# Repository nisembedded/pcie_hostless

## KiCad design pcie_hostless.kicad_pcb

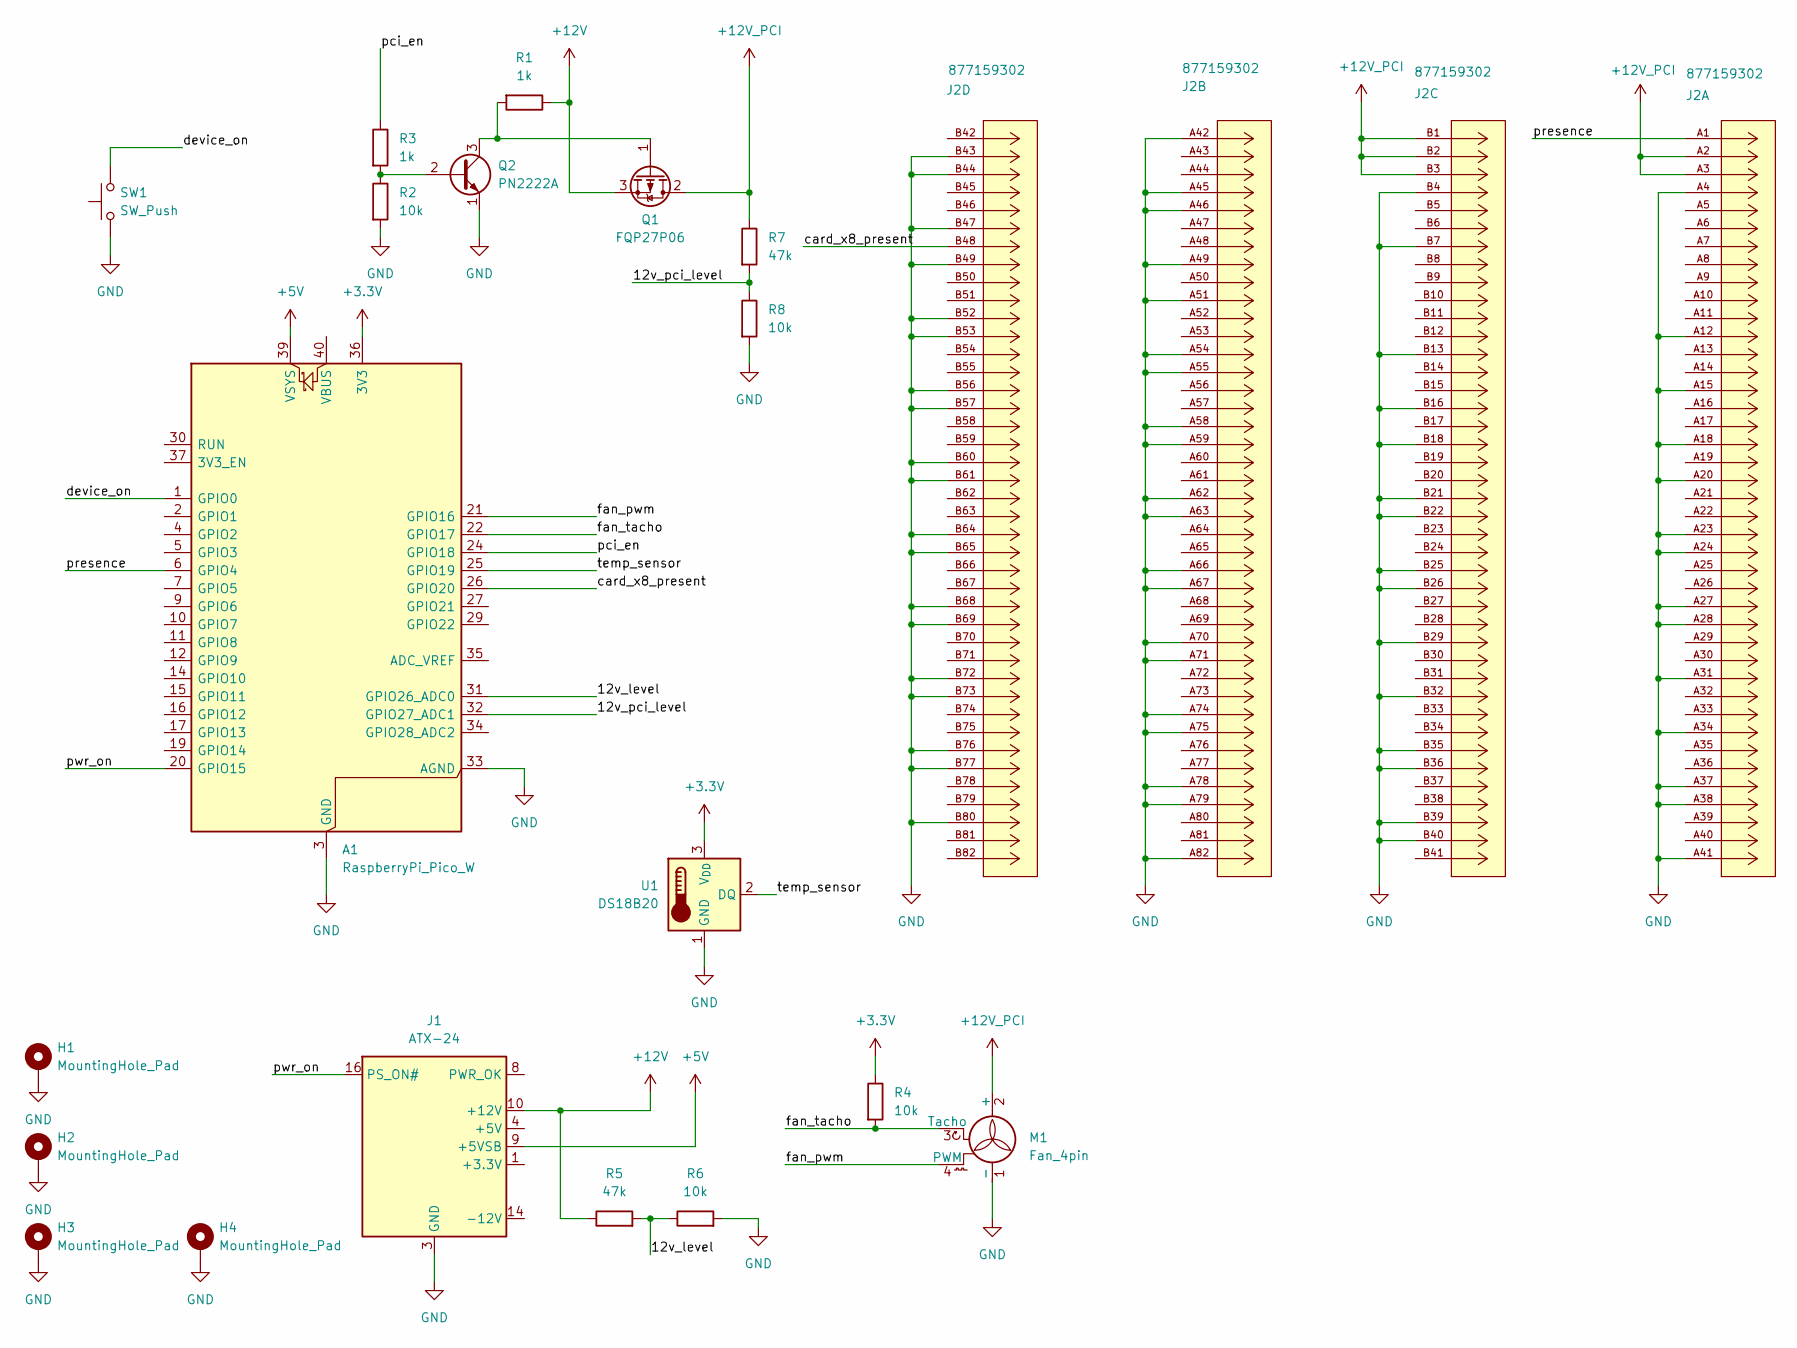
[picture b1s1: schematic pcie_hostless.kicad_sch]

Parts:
A1: RaspberryPi_Pico_W; RaspberryPi_Pico_Common_THT
H1, H2, H3, H4: MountingHole_Pad; MountingHole_3.5mm_Pad_Via
J1: ATX-24; Molex_Mini-Fit_Jr_5566-24A2_2x12_P4.20mm_Vertical
J2: 877159302; CONN_87715-9302_MOL; MANUFACTURER_PART_NUMBER 877159302
M1: Fan_4pin; FanPinHeader_1x04_P2.54mm_Vertical
Q1: FQP27P06; TO-220-3_Vertical
Q2: PN2222A; TO-92_Inline
R1, R3: 1k; R_0805_2012Metric
R2, R4, R6, R8: 10k; R_0805_2012Metric
R5, R7: 47k; R_0805_2012Metric
SW1: SW_Push; SW_Tactile_SKHH_Angled
U1: DS18B20; TO-92_Inline

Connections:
+3.3V: A1.36 (3V3), R4.1, U1.3 (V_{DD})
+5V: A1.39 (VSYS), J1.9 (+5VSB)
+12V: J1.10 (+12V), J1.11 (+12V), Q1.3 (S), R1.1, R5.1
+12V_PCI: J2.A2, J2.A3, J2.B1, J2.B2, J2.B3, M1.2 (+), Q1.2 (D), R7.1
/12v_level: A1.31 (GPIO26_ADC0), R5.2, R6.1
/12v_pci_level: A1.32 (GPIO27_ADC1), R7.2, R8.1
/card_x8_present: A1.26 (GPIO20), J2.B48
/device_on: A1.1 (GPIO0), SW1.2
/fan_pwm: A1.21 (GPIO16), M1.4 (PWM)
/fan_tacho: A1.22 (GPIO17), M1.3 (Tacho), R4.2
/pci_en: A1.24 (GPIO18), R3.1
/presence: A1.6 (GPIO4), J2.A1
/pwr_on: A1.20 (GPIO15), J1.16 (PS_ON#)
/temp_sensor: A1.25 (GPIO19), U1.2 (DQ)
GND: A1.3 (GND), A1.8 (GND), A1.13 (GND), A1.18 (GND), A1.23 (GND), A1.28 (GND), A1.33 (AGND), A1.38 (GND), H1.1, H2.1, H3.1, H4.1, J1.3 (GND), J1.5 (GND), J1.7 (GND), J1.15 (GND), J1.17 (GND), J1.18 (GND), J1.19 (GND), J1.24 (GND), J2.A4, J2.A12, J2.A15, J2.A18, J2.A20, J2.A23, J2.A24, J2.A27, J2.A28, J2.A31, J2.A34, J2.A37, J2.A38, J2.A41, J2.A42, J2.A45, J2.A46, J2.A49, J2.A51, J2.A54, J2.A55, J2.A58, J2.A59, J2.A62, J2.A63, J2.A66, J2.A67, J2.A70, J2.A71, J2.A74, J2.A75, J2.A78, J2.A79, J2.A82, J2.B4, J2.B7, J2.B13, J2.B16, J2.B18, J2.B21, J2.B22, J2.B25, J2.B26, J2.B29, J2.B32, J2.B35, J2.B36, J2.B39, J2.B40, J2.B43, J2.B44, J2.B47, J2.B49, J2.B52, J2.B53, J2.B56, J2.B57, J2.B60, J2.B61, J2.B64, J2.B65, J2.B68, J2.B69, J2.B72, J2.B73, J2.B76, J2.B77, J2.B80, M1.1 (-), Q2.1 (E), R2.2, R6.2, R8.2, SW1.1, U1.1 (GND)
unnamed: J1.1 (+3.3V), J1.2 (+3.3V), J1.12 (+3.3V), J1.13 (+3.3V)
unnamed: J1.4 (+5V), J1.6 (+5V), J1.21 (+5V), J1.22 (+5V), J1.23 (+5V)
unnamed: Q1.1 (G), Q2.3 (C), R1.2
unnamed: Q2.2 (B), R2.1, R3.2

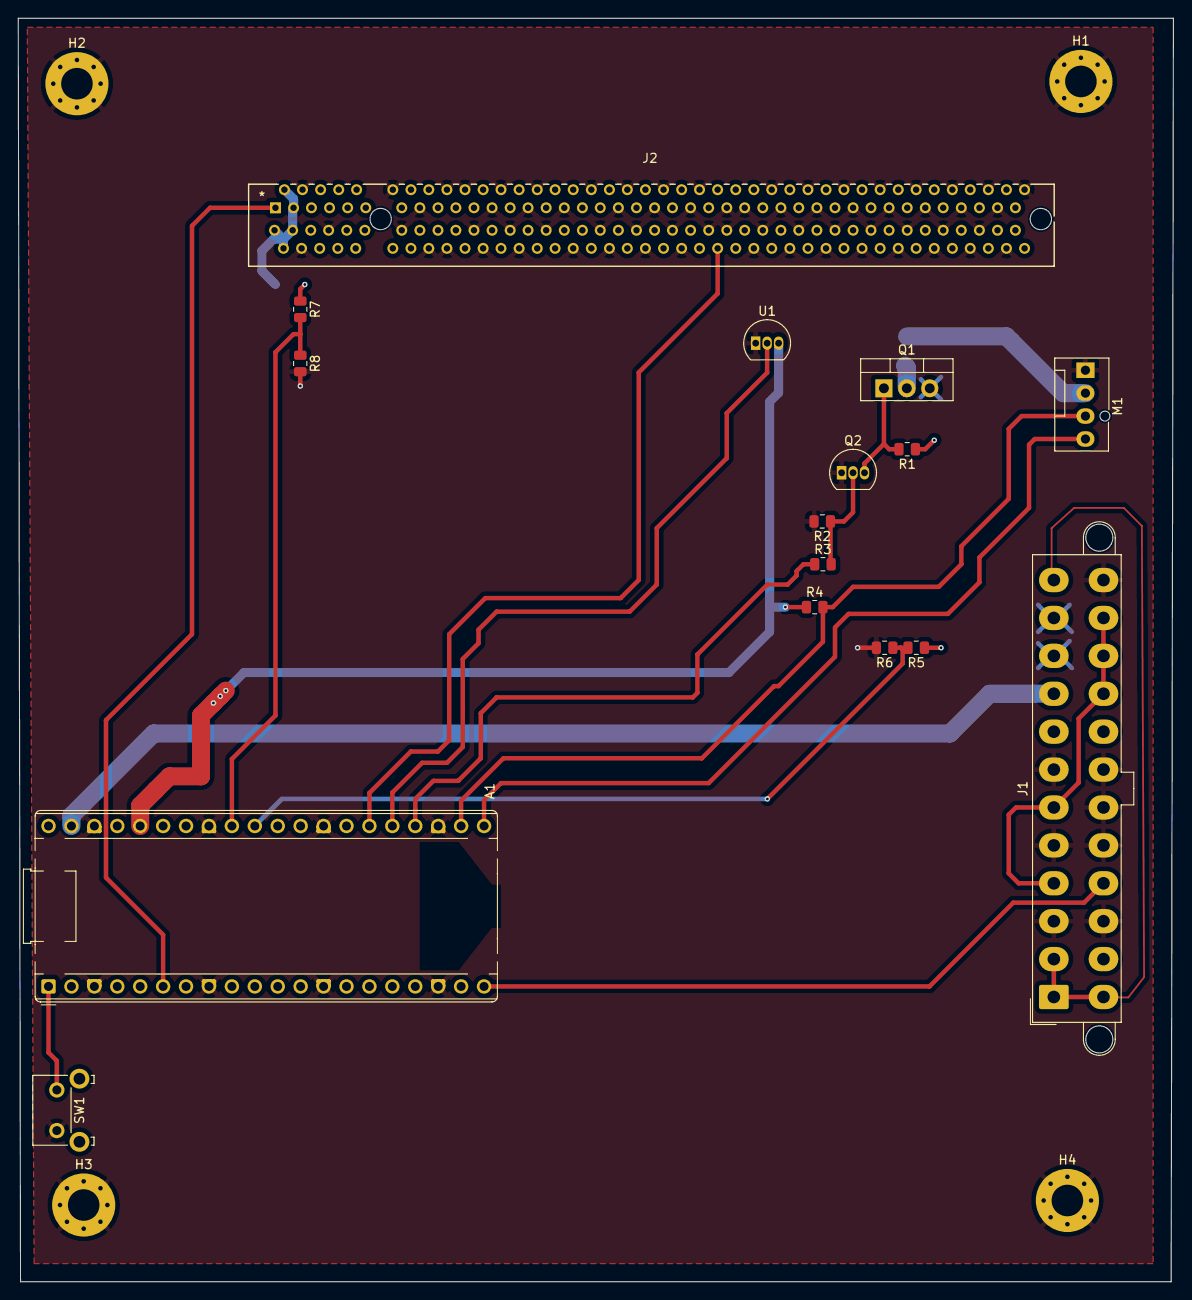
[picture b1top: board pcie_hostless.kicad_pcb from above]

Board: 2 copper layers, 128.0 x 140.0 mm, 20 parts (0 on the bottom side), 19 nets.

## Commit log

2025-05-07 Add first draft version of board
2025-05-07 Add README.md to project
2025-05-07 Fix naming of README.md
